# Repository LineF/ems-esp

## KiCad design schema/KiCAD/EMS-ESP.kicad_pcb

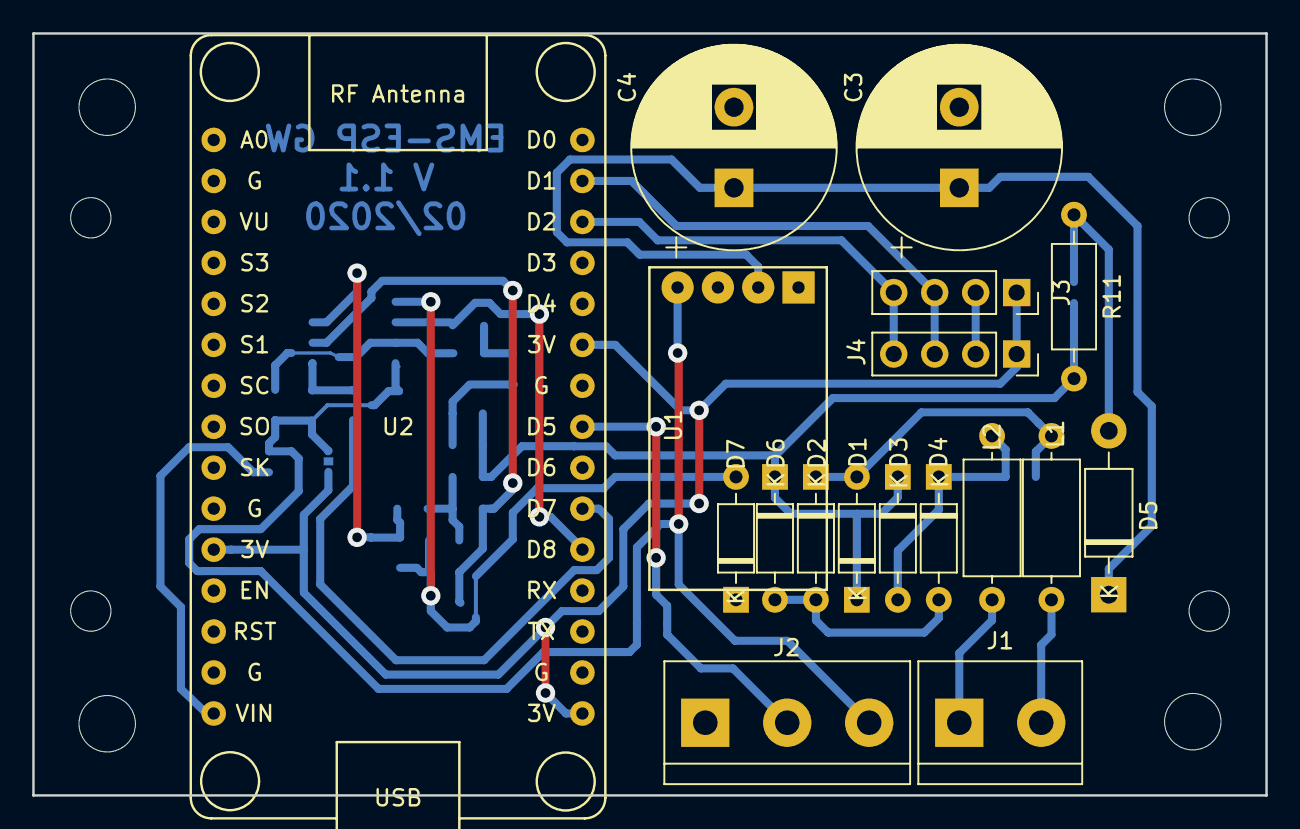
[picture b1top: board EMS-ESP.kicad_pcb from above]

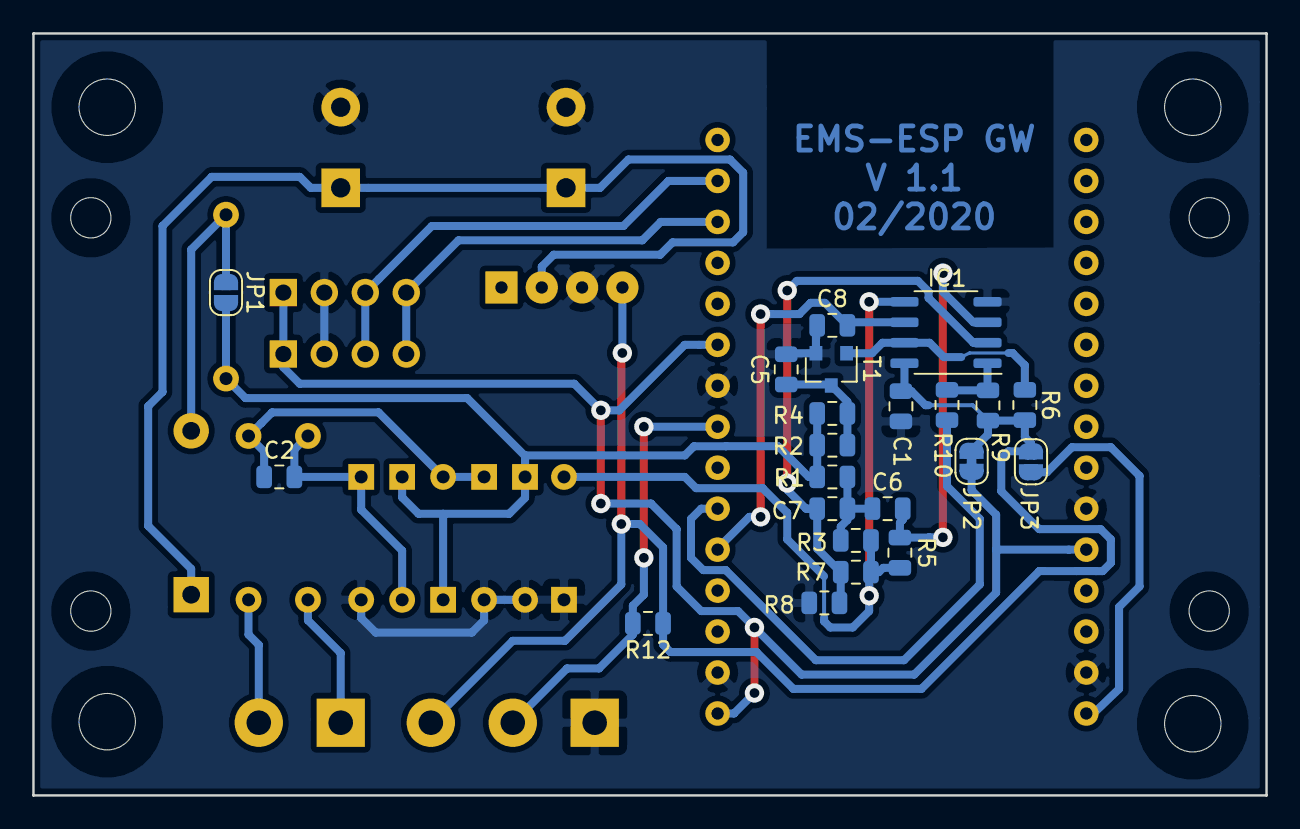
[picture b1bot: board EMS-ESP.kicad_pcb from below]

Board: 2 copper layers, 76.5 x 47.2 mm, 40 parts (22 on the bottom side), 23 nets.

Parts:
C1: 100n; C_0805_2012Metric
C2: 68p; C_0805_2012Metric
C3, C4: 820u; CP_Radial_D12.5mm_P5.00mm
C5: 1.5n; C_0805_2012Metric
C6: 10u; C_0805_2012Metric
C7: 1n; C_0805_2012Metric
C8: 10n; C_0805_2012Metric
D1, D2, D3, D4, D6: BAT42; D_DO-35_SOD27_P7.62mm_Horizontal
D5: 1N4001; D_DO-41_SOD81_P10.16mm_Horizontal
D7: 1N4148; D_DO-35_SOD27_P7.62mm_Horizontal
IC1: LM393N; SO-8_3.9x4.9mm_P1.27mm
J1: EMS-Bus; TerminalBlock_bornier-2_P5.08mm
J2: DS18B20; TerminalBlock_bornier-3_P5.08mm
J3: I2C; PinSocket_1x04_P2.54mm_Vertical
J4: I2C-BMP180; PinSocket_1x04_P2.54mm_Vertical
JP1, JP3: SolderJumper-2_P1.3mm_Open_RoundedPad1.0x1.5mm
JP2: SolderJumper-2_P1.3mm_Bridged_RoundedPad1.0x1.5mm
L1, L2: 4.7uH; L_Axial_L7.0mm_D3.3mm_P10.16mm_Horizontal_Fastron_MICC
R1, R7: 10K; R_0805_2012Metric
R2, R4: 330; R_0805_2012Metric
R3: 360; R_0805_2012Metric
R5: 47K; R_0805_2012Metric
R6, R9: 4K7; R_0805_2012Metric
R8: 100K; R_0805_2012Metric
R10: 100; R_0805_2012Metric
R11: 0; R_Axial_DIN0207_L6.3mm_D2.5mm_P10.16mm_Horizontal
R12: 4k7; R_0805_2012Metric
T1: BC847B; SOT-23
U1: DC-Buck_Converter_Chin01; DC-DC-Buck-Konverter
U2: NodeMCU_1.0_(ESP-12E); NodeMCU2.0Amica(12-E)

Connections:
+3V3: C1.2, IC1.8, J2.3, JP2.1, JP3.1, R6.1, R9.1, R12.1, U1.4
/3V3_ESP: J3.1, J4.1, JP2.2, U2.11, U2.16, U2.25
/DS: J2.2, R12.2, U2.23
/Rx: R10.2, U2.21
/SCL: J3.3, J4.3, U2.29
/SDA: J3.4, J4.4, U2.28
/Tx: C8.1, IC1.6, U2.20
/U_REF: D7.2, IC1.5, R3.2, R5.2, R7.2
GND: C1.1, C3.2, C4.2, C5.2, C8.2, D2.2, D4.2, D6.2, D7.1, IC1.4, J2.1, J3.2, J4.2, R8.2, T1.2, U1.3, U2.10, U2.14, U2.17, U2.24
unnamed: C2.1, D1.2, D2.1, L1.2
unnamed: C2.2, D3.2, D4.1, L2.2
unnamed: C3.1, C4.1, D5.1, U1.2
unnamed: C5.1, R2.2, R4.2, T1.3
unnamed: C6.1, C7.1, R1.1, R3.1
unnamed: C6.2, IC1.3, R5.1
unnamed: C7.2, IC1.2, R7.1, R8.1
unnamed: D1.1, D3.1, D6.1, JP1.2, R1.2, R2.1, R4.1, R11.2
unnamed: D5.2, JP1.1, R11.1
unnamed: IC1.1, R9.2, R10.1
unnamed: IC1.7, R6.2, T1.1
unnamed: J1.1, L2.1
unnamed: J1.2, L1.1
unnamed: JP3.2, U2.15

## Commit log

2020-01-05 add KiCAD project files
2020-01-05 add schema files and oszi pictures
2020-02-10 added pullup resistor for DS18B20 data line
2020-02-11 rearranged bucket converter, pinheader corrected
2020-02-17 big mqtt payload fix (for many sensors)
2020-02-20 retry publish, count #mqtt fails in system cmd - #264
2020-02-21 fix payload size
2020-02-26 fix payload size, add webbuilder script for nodemcuv2
2020-10-03 change ota upload address to absolute ip address
2020-10-25 set module default to esp8266, add pio_local.ini
